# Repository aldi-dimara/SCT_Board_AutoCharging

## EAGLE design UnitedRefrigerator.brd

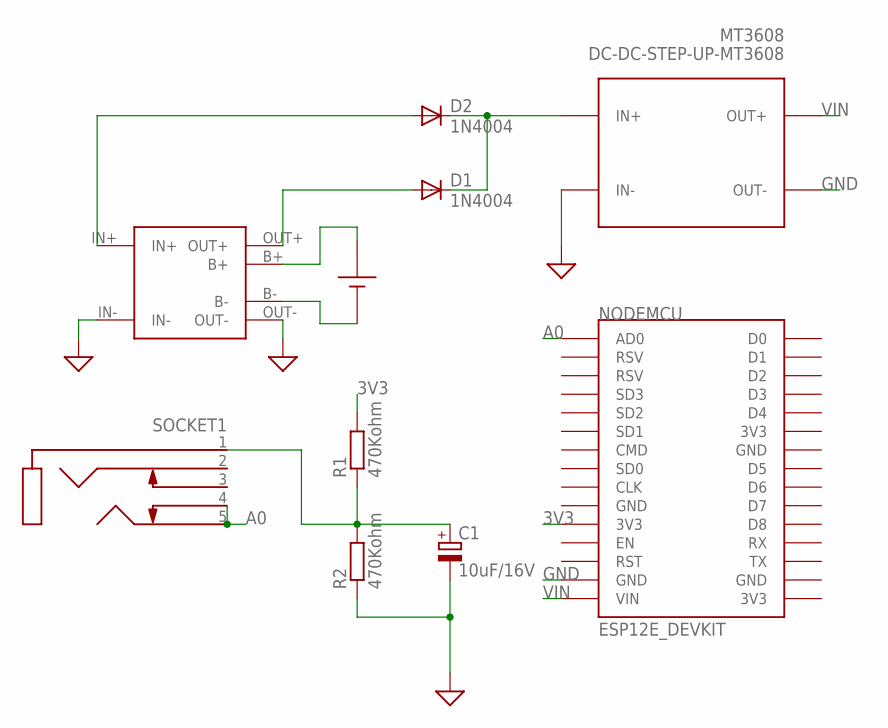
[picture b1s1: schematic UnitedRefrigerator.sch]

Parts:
C1: 10uF/16V; E2,5-6
D1, D2: 1N4004; DO41-10
MT3608: DC-DC-STEP-UP-MT3608
NODEMCU: ESP12E_DEVKIT
R1, R2: 470Kohm; 0204/7
SOCKET1: STEREO_JACK3F07; 3.5AUDIO_3F07
TP4056: TP4056-MODULE; TP4056-LITHIUM-PROTECTED-MODULE
U$3: 18650CABLE; 18650-CASE-CABLE

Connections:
3V3: NODEMCU.3V3@0 (3V3), R1.2
A0: NODEMCU.AD0, SOCKET1.4 (RSWITCH), SOCKET1.5 (RING)
GND: C1.-, MT3608.IN-, MT3608.OUT-, NODEMCU.GND@1 (GND), R2.1, TP4056.IN-, TP4056.OUT-
unnamed: C1.+, R1.1, R2.2, SOCKET1.1 (SLEEVE)
unnamed: TP4056.B-, U$3.NEG
unnamed: TP4056.B+, U$3.POS
unnamed: D1.C, D2.C, MT3608.IN+
unnamed: D2.A, TP4056.IN+
unnamed: D1.A, TP4056.OUT+
VIN: MT3608.OUT+, NODEMCU.VIN

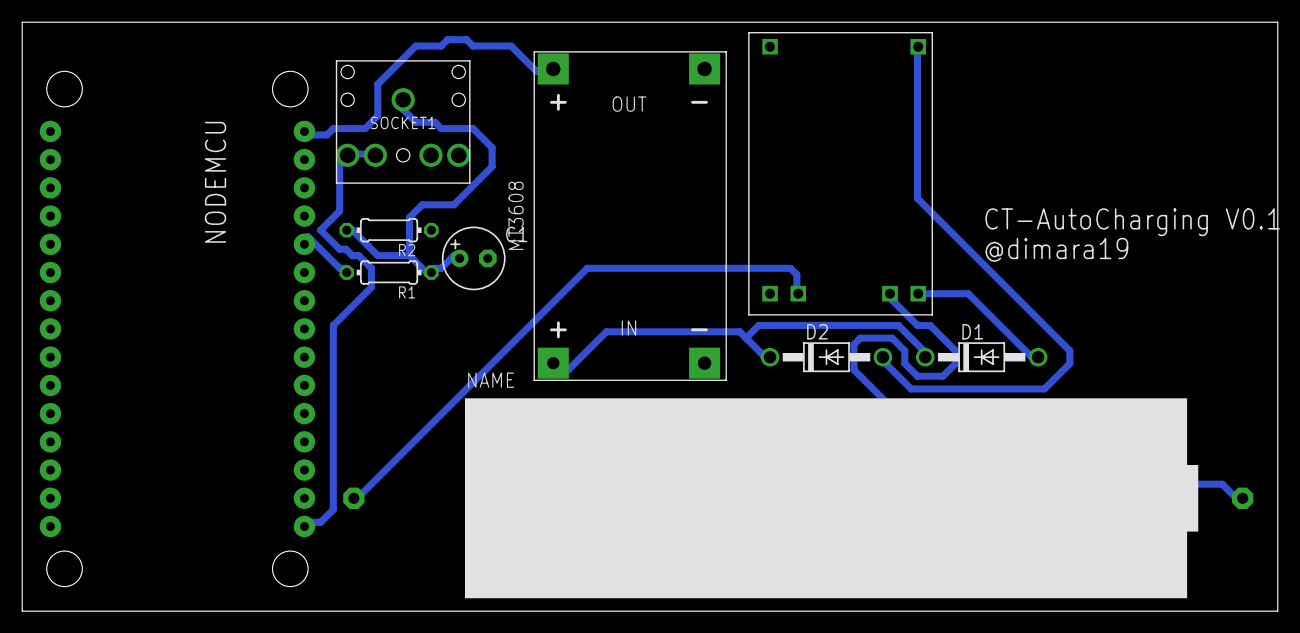
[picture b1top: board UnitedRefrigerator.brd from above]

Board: 2 copper layers, 113.0 x 53.0 mm, 10 parts (0 on the bottom side), 10 nets.
